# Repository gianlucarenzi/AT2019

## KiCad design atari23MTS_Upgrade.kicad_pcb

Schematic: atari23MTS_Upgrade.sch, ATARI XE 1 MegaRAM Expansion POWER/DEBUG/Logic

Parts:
C1: 10u; c_elec_5x5.3
C2: 22u; c_elec_5x5.3
C3: 47u; c_elec_5x5.3
CART1: ATARI-CARTRIDGE; ATARI-LEFT-CARTRIDGE
D1: LRED; LED_1206
D2: LYELLOW; LED_1206
DISABLE.MODE.1, DISABLE.MODE.2: CONN_01X02; Pin_Header_Straight_1x02
ECI1: ECIBUS; ATARI-XE-ECI-SLOT
EXTPWR1: CONN_01X04; Pin_Header_Angled_1x04
FT232RPi.1: CONN_01X03; Pin_Header_Straight_1x03
JP1, JP2: CONN_01X03; Pin_Header_Straight_1x03
L1, L2: INDUCTOR_SMALL; Choke_SMD_1206_Handsoldering
P1: CONN_01X01; Pin_Header_Straight_1x01
P2, P3, P4, P5: CONN_01X01; MountingHole
P6: CONN_01X01; Measurement_Point_Round-SMD-Pad_Small
R1: 330; R_1206_HandSoldering
R2, R4: 10K; R_1206_HandSoldering
R3: 220; R_1206_HandSoldering
STLinkV2.1, STLinkV2.2: CONN_01X04; Pin_Header_Angled_1x04
SW1, SW2: SW_Push; SW_SPST_FSMSM_3D
U1: NCP1117ST33T3G; SOT-223

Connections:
+5VDC: CART1.13 (VCC), ECI1.7 (VCC), EXTPWR1.1, L1.2, R1.1; also elsewhere on the board
A0: CART1.5 (A0); also elsewhere on the board
A1: CART1.4 (A1); also elsewhere on the board
A2: CART1.3 (A2); also elsewhere on the board
A3: CART1.2 (A3); also elsewhere on the board
A4: CART1.C (A4); also elsewhere on the board
A5: CART1.D (A5); also elsewhere on the board
A6: CART1.E (A6); also elsewhere on the board
A7: CART1.F (A7); also elsewhere on the board
A8: CART1.H (A8); also elsewhere on the board
A9: CART1.J (A9); also elsewhere on the board
A10: CART1.P (A10); also elsewhere on the board
A11: CART1.N (A11); also elsewhere on the board
A12: CART1.K (A12); also elsewhere on the board
A13: ECI1.D (A13); also elsewhere on the board
A14: ECI1.E (A14); also elsewhere on the board
A15: ECI1.F (A15); also elsewhere on the board
AUDIO: ECI1.5 (AUDIO); also elsewhere on the board
B02/PHI2: CART1.S (PHI2); also elsewhere on the board
BOOT0_CART: JP1.2; also elsewhere on the board
BOOT0_MEM: JP2.2; also elsewhere on the board
D0: CART1.10 (D0); also elsewhere on the board
D1: CART1.9 (D1); also elsewhere on the board
D2: CART1.8 (D2); also elsewhere on the board
D3: CART1.L (D3); also elsewhere on the board
D4: CART1.6 (D4); also elsewhere on the board
D5: CART1.7 (D5); also elsewhere on the board
D6: CART1.11 (D6); also elsewhere on the board
D7: CART1.M (D7); also elsewhere on the board
GND: C1.2, C2.2, C3.2, CART1.B (GND), D1.1 (K), D2.1 (K), DISABLE.MODE.1.2, DISABLE.MODE.2.2, ECI1.H (GND), EXTPWR1.2, EXTPWR1.3, FT232RPi.1.1, JP1.3, JP2.3, P1.1, STLinkV2.1.1, STLinkV2.2.1, SW1.1, SW2.1, U1.1 (GND); also elsewhere on the board
unnamed: C2.1, C3.1, L2.2, R3.1, U1.2 (VO)
unnamed: D1.2 (A), R1.2
unnamed: D2.2 (A), R3.2
R/~W: CART1.R (R/~W); also elsewhere on the board
RD4: CART1.A (RD4); also elsewhere on the board
RD5: CART1.14 (RD5); also elsewhere on the board
RSRVD: ECI1.A (RSRVD); also elsewhere on the board
SWDCLK_CART: STLinkV2.1.3; also elsewhere on the board
SWDCLK_MEM: STLinkV2.2.3; also elsewhere on the board
SWDIO_CART: STLinkV2.1.2; also elsewhere on the board
SWDIO_MEM: STLinkV2.2.2; also elsewhere on the board
TP1: P6.1; also elsewhere on the board
UART_RX: FT232RPi.1.2; also elsewhere on the board
UART_TX: FT232RPi.1.3; also elsewhere on the board
VCC3V3: JP1.1, JP2.1, L2.1, R2.2, R4.2, STLinkV2.1.4, STLinkV2.2.4; also elsewhere on the board
VCC5V: C1.1, L1.1, U1.3 (VI); also elsewhere on the board
nRESET_CART: DISABLE.MODE.1.1, R2.1, SW1.2; also elsewhere on the board
nRESET_MEM: DISABLE.MODE.2.1, R4.1, SW2.2; also elsewhere on the board
~CCTL: CART1.15 (~CCTL); also elsewhere on the board
~D1XX: ECI1.3 (~D1XX); also elsewhere on the board
~EXSEL: ECI1.1 (~EXSEL); also elsewhere on the board
~HALT: ECI1.C (~HALT); also elsewhere on the board
~IRQ: ECI1.B (~IRQ); also elsewhere on the board
~MPD: ECI1.4 (~MPD); also elsewhere on the board
~REF: ECI1.6 (~REF); also elsewhere on the board
~RST: ECI1.2 (~RST); also elsewhere on the board
~S4: CART1.1 (~S4); also elsewhere on the board
~S5: CART1.12 (~S5); also elsewhere on the board

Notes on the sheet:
POWER SECTION
DEBUG/PROGRAMMING SECTION MEMORY
ATARI CONNECTIONS
MOUNTING HOLES
BOOTSEL CART
RESET BUTTON CART
RESET BUTTON MEM
DEBUG/PROGRAMMING SECTION CART
BOOTSEL MEM

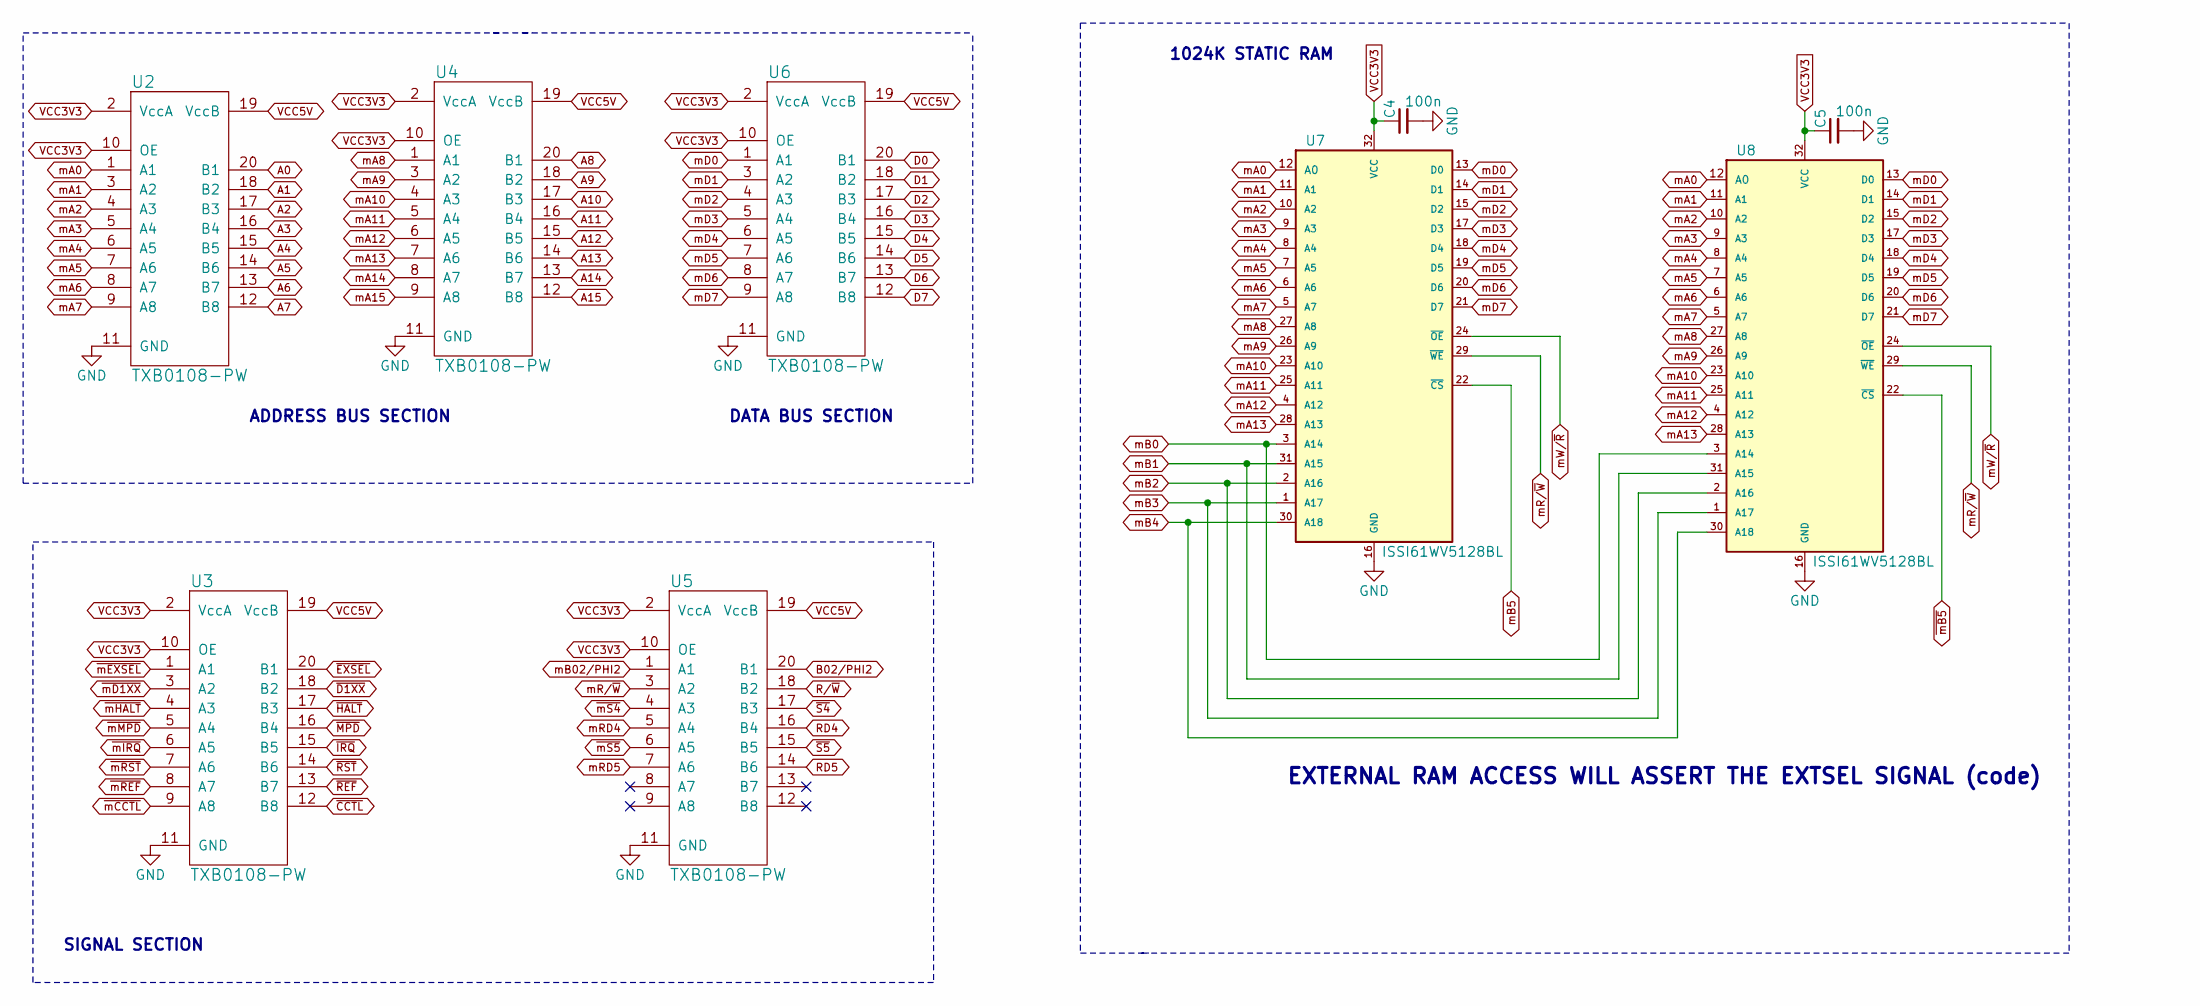
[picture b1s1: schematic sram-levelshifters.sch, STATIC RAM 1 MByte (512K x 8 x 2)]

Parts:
C4, C5: 100n; C_1206_HandSoldering
U2, U3, U4, U5, U6: TXB0108-PW; SSOP-20_4.4x6.5mm_Pitch0.65mm
U7, U8: ISSI61WV5128BL; SOP-32L-20.5x11.30-1.27mm

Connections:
A0: U2.20 (B1); also elsewhere on the board
A1: U2.18 (B2); also elsewhere on the board
A2: U2.17 (B3); also elsewhere on the board
A3: U2.16 (B4); also elsewhere on the board
A4: U2.15 (B5); also elsewhere on the board
A5: U2.14 (B6); also elsewhere on the board
A6: U2.13 (B7); also elsewhere on the board
A7: U2.12 (B8); also elsewhere on the board
A8: U4.20 (B1); also elsewhere on the board
A9: U4.18 (B2); also elsewhere on the board
A10: U4.17 (B3); also elsewhere on the board
A11: U4.16 (B4); also elsewhere on the board
A12: U4.15 (B5); also elsewhere on the board
A13: U4.14 (B6); also elsewhere on the board
A14: U4.13 (B7); also elsewhere on the board
A15: U4.12 (B8); also elsewhere on the board
B02/PHI2: U5.20 (B1); also elsewhere on the board
D0: U6.20 (B1); also elsewhere on the board
D1: U6.18 (B2); also elsewhere on the board
D2: U6.17 (B3); also elsewhere on the board
D3: U6.16 (B4); also elsewhere on the board
D4: U6.15 (B5); also elsewhere on the board
D5: U6.14 (B6); also elsewhere on the board
D6: U6.13 (B7); also elsewhere on the board
D7: U6.12 (B8); also elsewhere on the board
GND: C4.2, C5.2, U2.11 (GND), U3.11 (GND), U4.11 (GND), U5.11 (GND), U6.11 (GND), U7.16 (GND), U8.16 (GND); also elsewhere on the board
R/~W: U5.18 (B2); also elsewhere on the board
RD4: U5.16 (B4); also elsewhere on the board
RD5: U5.14 (B6); also elsewhere on the board
VCC3V3: C4.1, C5.1, U2.2 (VccA), U2.10 (OE), U3.2 (VccA), U3.10 (OE), U4.2 (VccA), U4.10 (OE), U5.2 (VccA), U5.10 (OE), U6.2 (VccA), U6.10 (OE), U7.32 (VCC), U8.32 (VCC); also elsewhere on the board
VCC5V: U2.19 (VccB), U3.19 (VccB), U4.19 (VccB), U5.19 (VccB), U6.19 (VccB); also elsewhere on the board
mA0: U2.1 (A1), U7.12 (A0), U8.12 (A0); also elsewhere on the board
mA1: U2.3 (A2), U7.11 (A1), U8.11 (A1); also elsewhere on the board
mA2: U2.4 (A3), U7.10 (A2), U8.10 (A2); also elsewhere on the board
mA3: U2.5 (A4), U7.9 (A3), U8.9 (A3); also elsewhere on the board
mA4: U2.6 (A5), U7.8 (A4), U8.8 (A4); also elsewhere on the board
mA5: U2.7 (A6), U7.7 (A5), U8.7 (A5); also elsewhere on the board
mA6: U2.8 (A7), U7.6 (A6), U8.6 (A6); also elsewhere on the board
mA7: U2.9 (A8), U7.5 (A7), U8.5 (A7); also elsewhere on the board
mA8: U4.1 (A1), U7.27 (A8), U8.27 (A8); also elsewhere on the board
mA9: U4.3 (A2), U7.26 (A9), U8.26 (A9); also elsewhere on the board
mA10: U4.4 (A3), U7.23 (A10), U8.23 (A10); also elsewhere on the board
mA11: U4.5 (A4), U7.25 (A11), U8.25 (A11); also elsewhere on the board
mA12: U4.6 (A5), U7.4 (A12), U8.4 (A12); also elsewhere on the board
mA13: U4.7 (A6), U7.28 (A13), U8.28 (A13); also elsewhere on the board
mA14: U4.8 (A7); also elsewhere on the board
mA15: U4.9 (A8); also elsewhere on the board
mB0: U7.3 (A14), U8.3 (A14); also elsewhere on the board
mB1: U7.31 (A15), U8.31 (A15); also elsewhere on the board
mB2: U7.2 (A16), U8.2 (A16); also elsewhere on the board
mB02/PHI2: U5.1 (A1); also elsewhere on the board
mB3: U7.1 (A17), U8.1 (A17); also elsewhere on the board
mB4: U7.30 (A18), U8.30 (A18); also elsewhere on the board
mB5: U7.22 (~CS); also elsewhere on the board
mD0: U6.1 (A1), U7.13 (D0), U8.13 (D0); also elsewhere on the board
mD1: U6.3 (A2), U7.14 (D1), U8.14 (D1); also elsewhere on the board
mD2: U6.4 (A3), U7.15 (D2), U8.15 (D2); also elsewhere on the board
mD3: U6.5 (A4), U7.17 (D3), U8.17 (D3); also elsewhere on the board
mD4: U6.6 (A5), U7.18 (D4), U8.18 (D4); also elsewhere on the board
mD5: U6.7 (A6), U7.19 (D5), U8.19 (D5); also elsewhere on the board
mD6: U6.8 (A7), U7.20 (D6), U8.20 (D6); also elsewhere on the board
mD7: U6.9 (A8), U7.21 (D7), U8.21 (D7); also elsewhere on the board
mR/~W: U5.3 (A2), U7.29 (~WE), U8.29 (~WE); also elsewhere on the board
mRD4: U5.5 (A4); also elsewhere on the board
mRD5: U5.7 (A6); also elsewhere on the board
mW/~R: U7.24 (~OE), U8.24 (~OE); also elsewhere on the board
~CCTL: U3.12 (B8); also elsewhere on the board
~D1XX: U3.18 (B2); also elsewhere on the board
~EXSEL: U3.20 (B1); also elsewhere on the board
~HALT: U3.17 (B3); also elsewhere on the board
~IRQ: U3.15 (B5); also elsewhere on the board
~MPD: U3.16 (B4); also elsewhere on the board
~REF: U3.13 (B7); also elsewhere on the board
~RST: U3.14 (B6); also elsewhere on the board
~S4: U5.17 (B3); also elsewhere on the board
~S5: U5.15 (B5); also elsewhere on the board
~mB5: U8.22 (~CS); also elsewhere on the board
~mCCTL: U3.9 (A8); also elsewhere on the board
~mD1XX: U3.3 (A2); also elsewhere on the board
~mEXSEL: U3.1 (A1); also elsewhere on the board
~mHALT: U3.4 (A3); also elsewhere on the board
~mIRQ: U3.6 (A5); also elsewhere on the board
~mMPD: U3.5 (A4); also elsewhere on the board
~mREF: U3.8 (A7); also elsewhere on the board
~mRST: U3.7 (A6); also elsewhere on the board
~mS4: U5.4 (A3); also elsewhere on the board
~mS5: U5.6 (A5); also elsewhere on the board

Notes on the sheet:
ADDRESS BUS SECTION
DATA BUS SECTION
SIGNAL SECTION
1024K STATIC RAM
EXTERNAL RAM ACCESS WILL ASSERT THE EXTSEL SIGNAL (code)

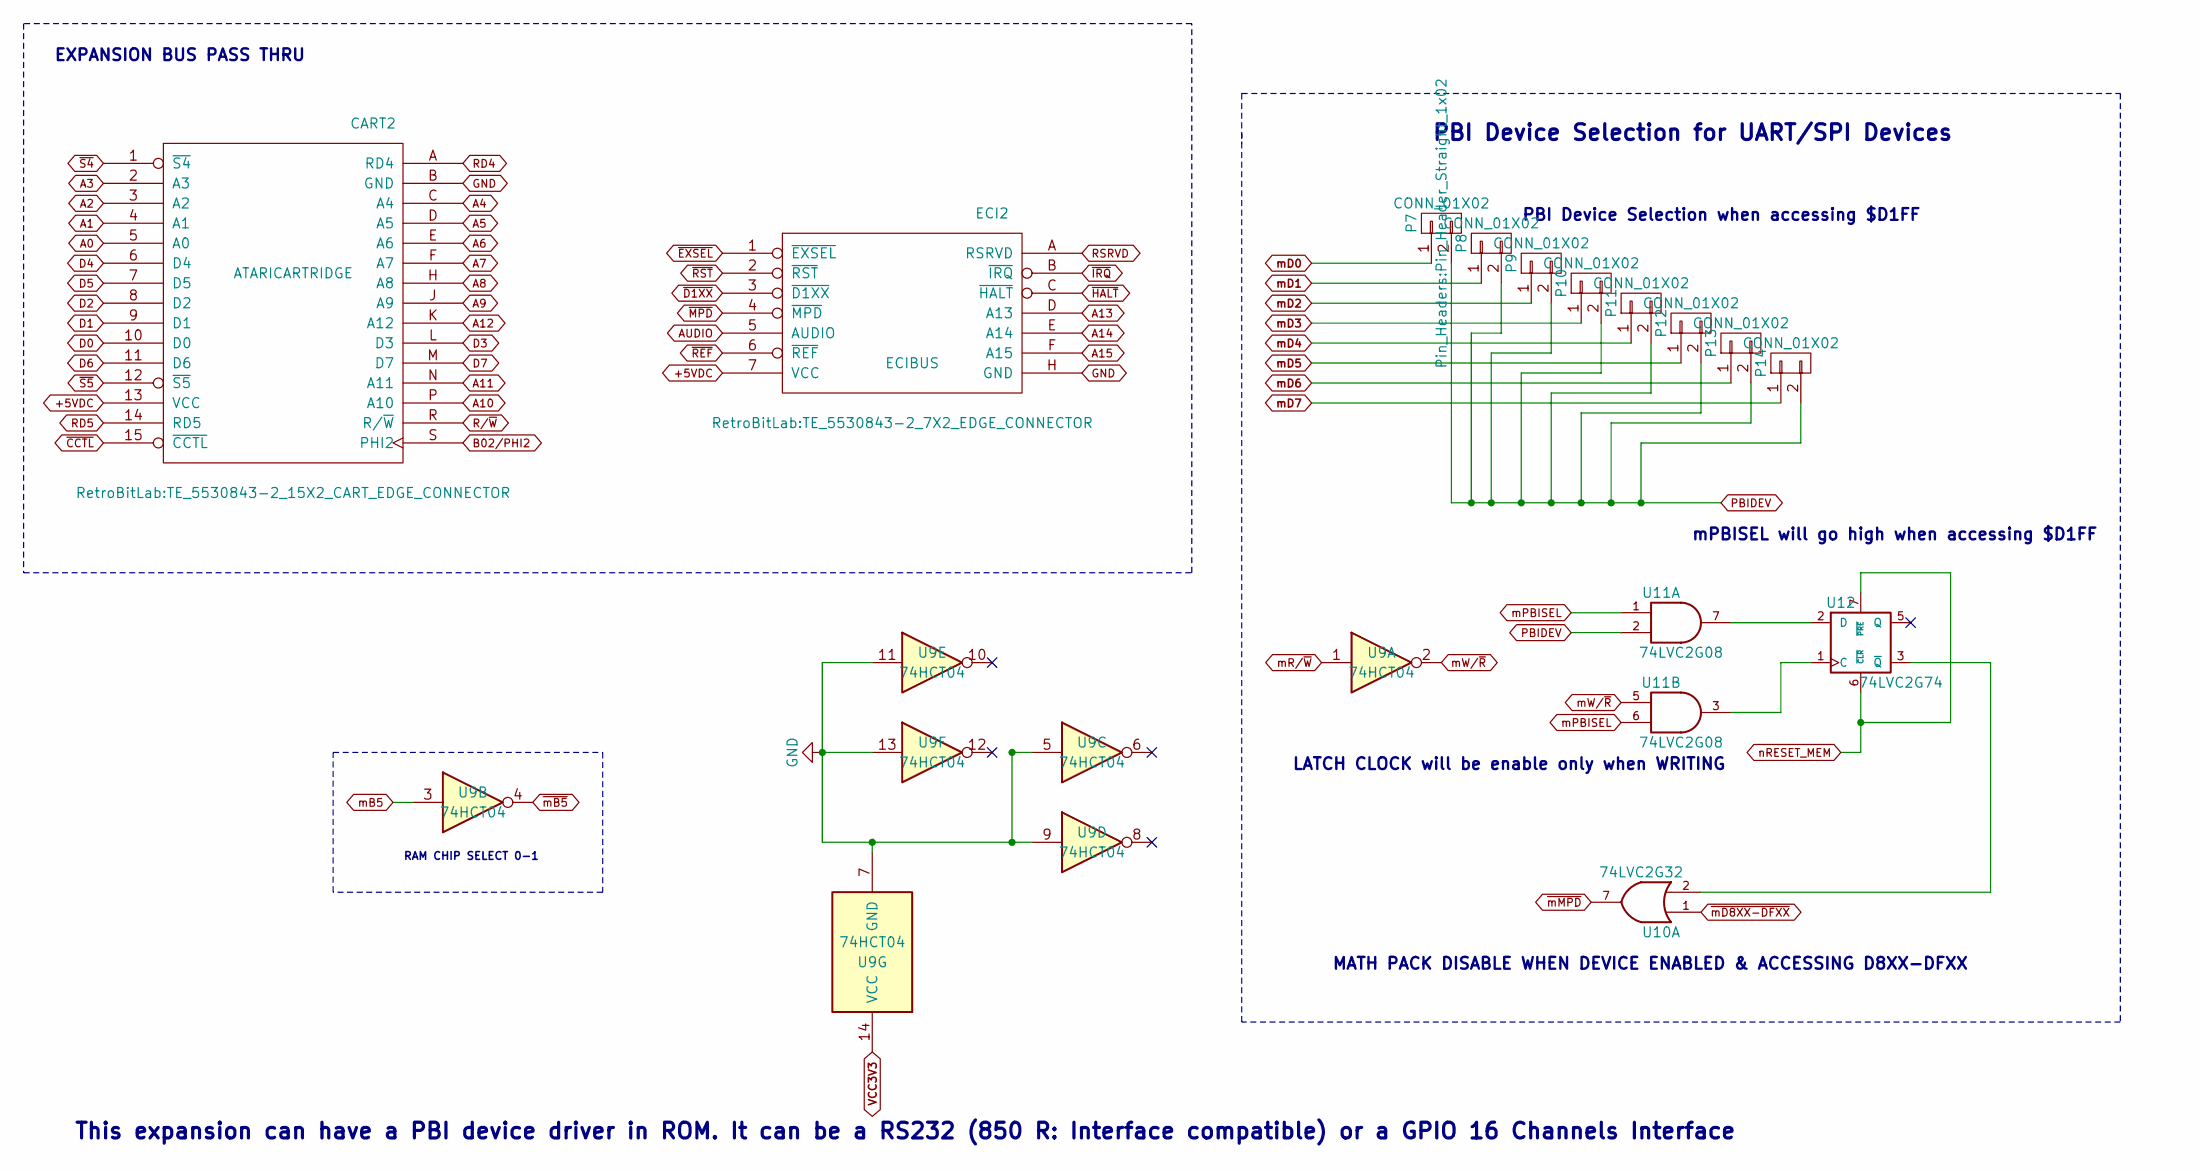
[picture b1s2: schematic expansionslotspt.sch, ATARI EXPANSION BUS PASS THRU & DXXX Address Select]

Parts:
CART2: ATARICARTRIDGE; TE_5530843-2_15X2_CART_EDGE_CONNECTOR
ECI2: ECIBUS; TE_5530843-2_7X2_EDGE_CONNECTOR
P7, P8, P9, P10, P11, P12, P13, P14: CONN_01X02; Pin_Header_Straight_1x02
U9: 74HCT04; SSOP-14_5.3x6.2mm_Pitch0.65mm
U10: 74LVC2G32; TSSOP-8_3x3mm_Pitch0.65mm
U11: 74LVC2G08; TSSOP-8_3x3mm_Pitch0.65mm
U12: 74LVC2G74; TSSOP-8_3x3mm_Pitch0.65mm

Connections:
+5VDC: CART2.13 (VCC), ECI2.7 (VCC), U10.8 (VCC), U11.8 (VCC), U12.8 (VCC); also elsewhere on the board
A0: CART2.5 (A0); also elsewhere on the board
A1: CART2.4 (A1); also elsewhere on the board
A2: CART2.3 (A2); also elsewhere on the board
A3: CART2.2 (A3); also elsewhere on the board
A4: CART2.C (A4); also elsewhere on the board
A5: CART2.D (A5); also elsewhere on the board
A6: CART2.E (A6); also elsewhere on the board
A7: CART2.F (A7); also elsewhere on the board
A8: CART2.H (A8); also elsewhere on the board
A9: CART2.J (A9); also elsewhere on the board
A10: CART2.P (A10); also elsewhere on the board
A11: CART2.N (A11); also elsewhere on the board
A12: CART2.K (A12); also elsewhere on the board
A13: ECI2.D (A13); also elsewhere on the board
A14: ECI2.E (A14); also elsewhere on the board
A15: ECI2.F (A15); also elsewhere on the board
AUDIO: ECI2.5 (AUDIO); also elsewhere on the board
B02/PHI2: CART2.S (PHI2); also elsewhere on the board
D0: CART2.10 (D0); also elsewhere on the board
D1: CART2.9 (D1); also elsewhere on the board
D2: CART2.8 (D2); also elsewhere on the board
D3: CART2.L (D3); also elsewhere on the board
D4: CART2.6 (D4); also elsewhere on the board
D5: CART2.7 (D5); also elsewhere on the board
D6: CART2.11 (D6); also elsewhere on the board
D7: CART2.M (D7); also elsewhere on the board
GND: CART2.B (GND), ECI2.H (GND), U9.5, U9.7 (GND), U9.9, U9.11, U9.13, U10.4 (GND), U11.4 (GND), U12.4 (GND); also elsewhere on the board
unnamed: U10.2, U12.3 (~Q)
unnamed: U11.3, U12.1 (C)
unnamed: U11.7, U12.2 (D)
PBIDEV: P7.2, P8.2, P9.2, P10.2, P11.2, P12.2, P13.2, P14.2, U11.2
R/~W: CART2.R (R/~W); also elsewhere on the board
RD4: CART2.A (RD4); also elsewhere on the board
RD5: CART2.14 (RD5); also elsewhere on the board
RSRVD: ECI2.A (RSRVD); also elsewhere on the board
VCC3V3: U9.14 (VCC); also elsewhere on the board
mB5: U9.3; also elsewhere on the board
mD0: P7.1; also elsewhere on the board
mD1: P8.1; also elsewhere on the board
mD2: P9.1; also elsewhere on the board
mD3: P10.1; also elsewhere on the board
mD4: P11.1; also elsewhere on the board
mD5: P12.1; also elsewhere on the board
mD6: P13.1; also elsewhere on the board
mD7: P14.1; also elsewhere on the board
mPBISEL: U11.1, U11.6; also elsewhere on the board
mR/~W: U9.1; also elsewhere on the board
mW/~R: U9.2, U11.5; also elsewhere on the board
nRESET_MEM: U12.6 (~CLR), U12.7 (~PRE); also elsewhere on the board
~CCTL: CART2.15 (~CCTL); also elsewhere on the board
~D1XX: ECI2.3 (~D1XX); also elsewhere on the board
~EXSEL: ECI2.1 (~EXSEL); also elsewhere on the board
~HALT: ECI2.C (~HALT); also elsewhere on the board
~IRQ: ECI2.B (~IRQ); also elsewhere on the board
~MPD: ECI2.4 (~MPD); also elsewhere on the board
~REF: ECI2.6 (~REF); also elsewhere on the board
~RST: ECI2.2 (~RST); also elsewhere on the board
~S4: CART2.1 (~S4); also elsewhere on the board
~S5: CART2.12 (~S5); also elsewhere on the board
~mB5: U9.4; also elsewhere on the board
~mD8XX-DFXX: U10.1; also elsewhere on the board
~mMPD: U10.7; also elsewhere on the board

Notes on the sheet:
EXPANSION BUS PASS THRU
PBI Device Selection when accessing $D1FF
MATH PACK DISABLE WHEN DEVICE ENABLED & ACCESSING D8XX-DFXX
mPBISEL will go high when accessing $D1FF
LATCH CLOCK will be enable only when WRITING
PBI Device Selection for UART/SPI Devices
This expansion can have a PBI device driver in ROM. It can be a RS232 (850 R: Interface compatible) or a GPIO 16 Channels Interface
RAM CHIP SELECT 0-1

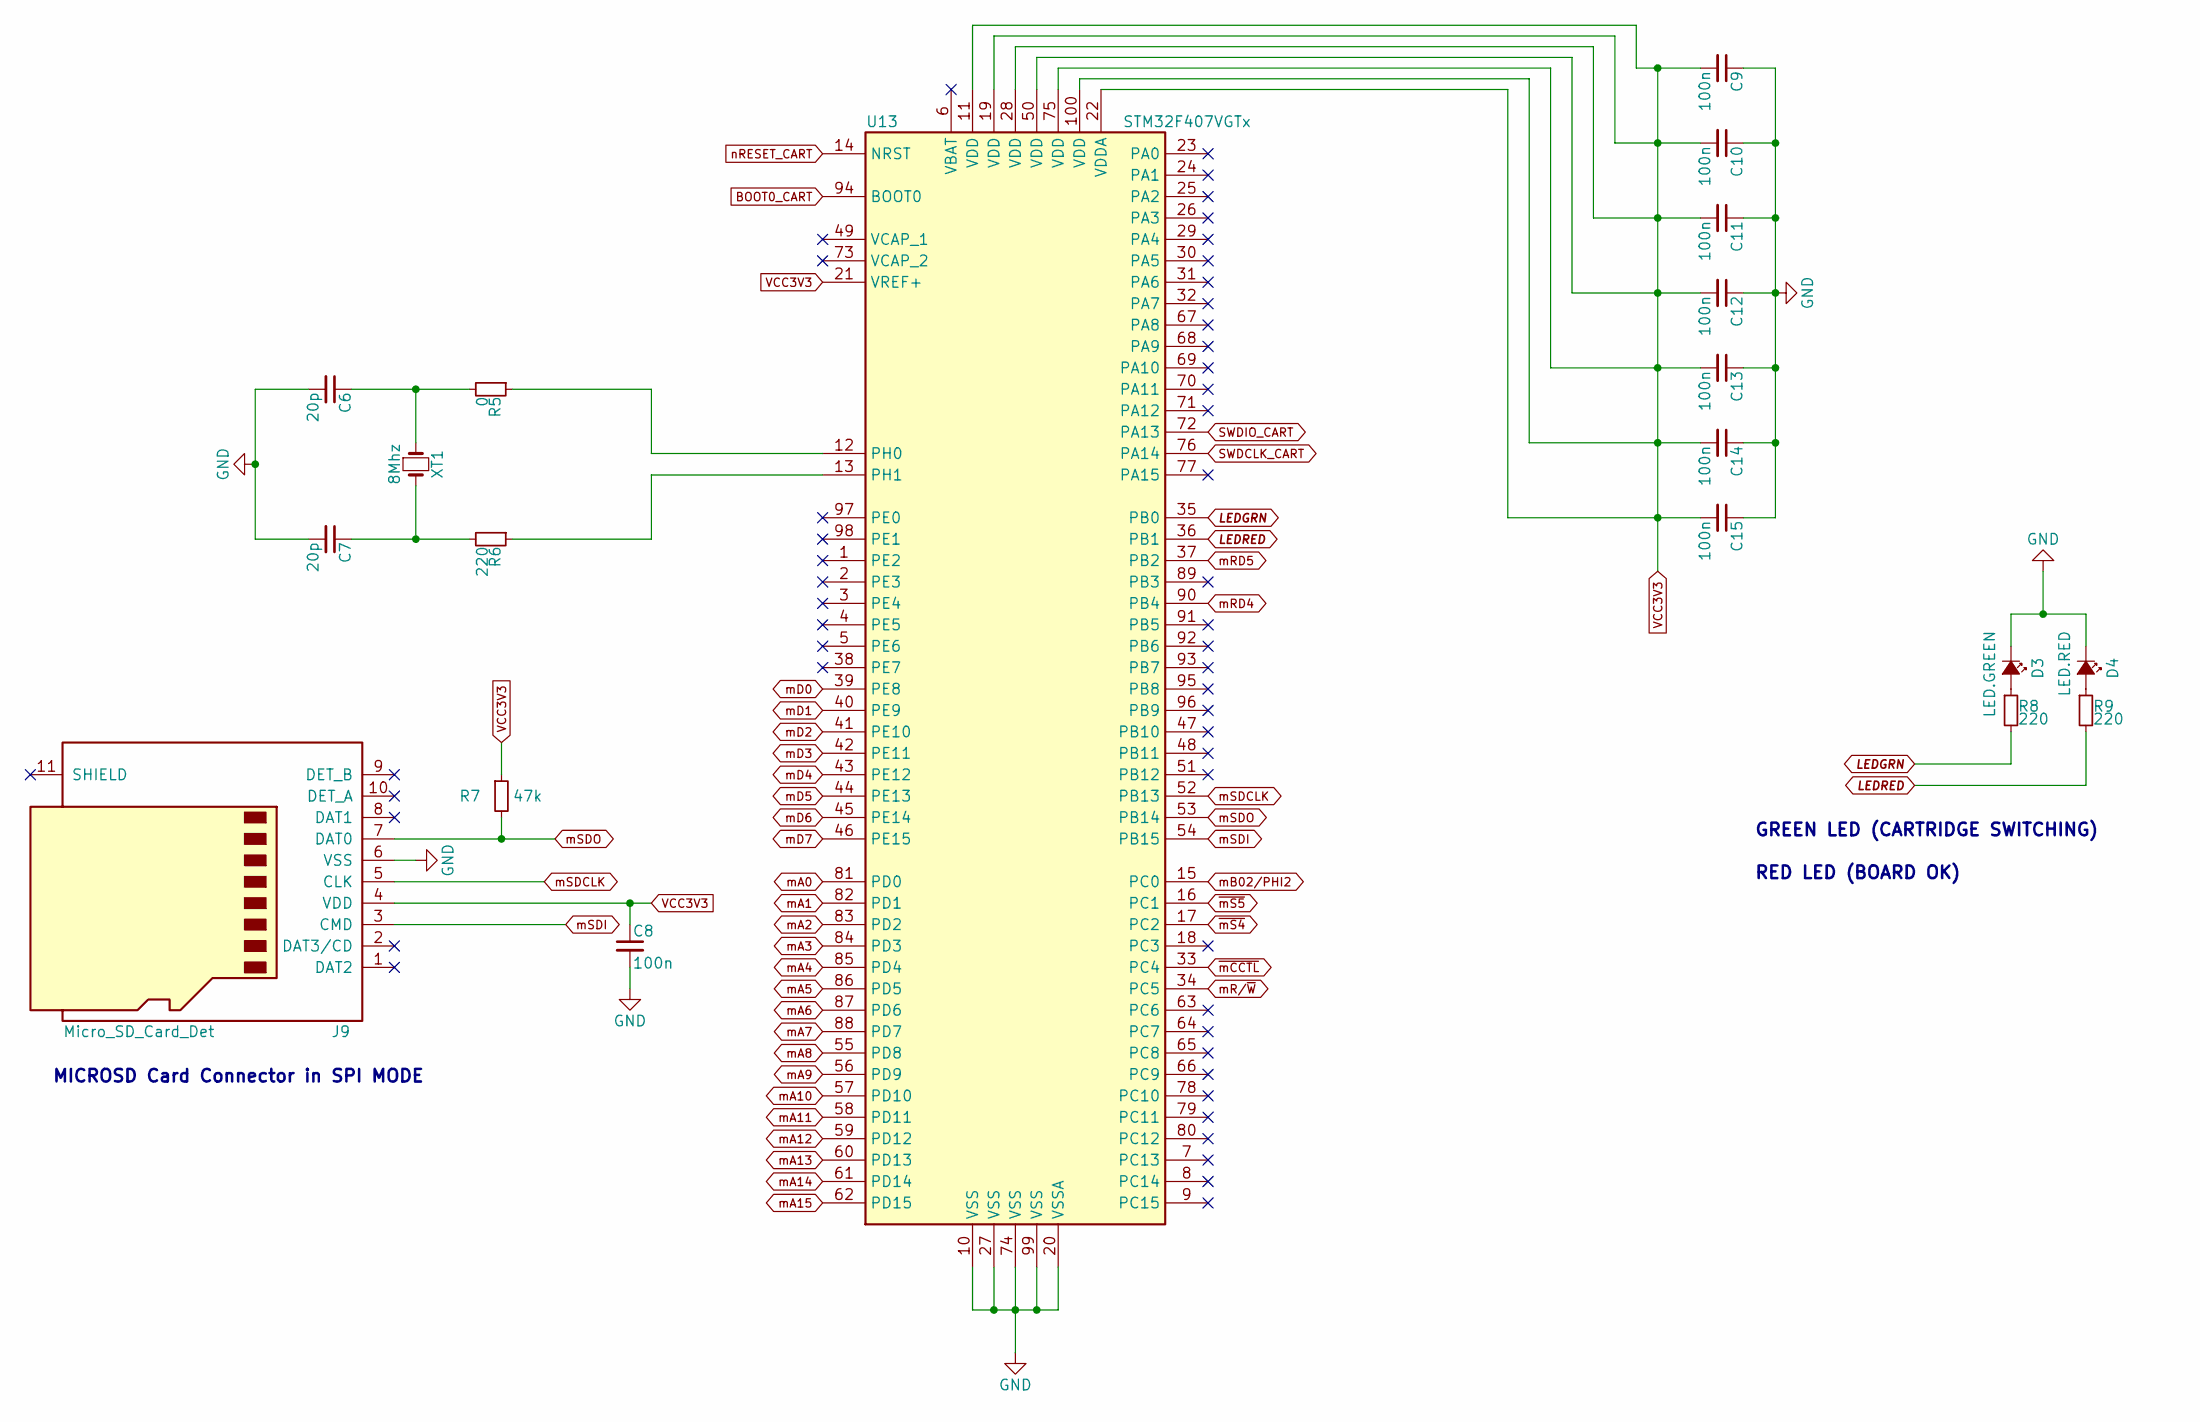
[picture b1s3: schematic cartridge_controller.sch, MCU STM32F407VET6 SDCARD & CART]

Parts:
C6, C7: 20p; C_1206_HandSoldering
C8, C9, C10, C11, C12, C13, C14, C15: 100n; C_1206_HandSoldering
D3: LED.GREEN; LED_1206
D4: LED.RED; LED_1206
J9: Micro_SD_Card_Det; microSD_HC_Hirose_DM3D-SF
R5: 0; R_1206_HandSoldering
R6, R8, R9: 220; R_1206_HandSoldering
R7: 47k; R_1206_HandSoldering
U13: STM32F407VGTx; TQFP-100_14x14mm_Pitch0.5mm
XT1: 8Mhz; Crystal_HC49-4H_Vertical_3D

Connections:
BOOT0_CART: U13.94 (BOOT0); also elsewhere on the board
GND: C6.2, C7.2, C8.2, C9.1, C10.1, C11.1, C12.1, C13.1, C14.1, C15.1, D3.1 (K), D4.1 (K), J9.6 (VSS), U13.10 (VSS), U13.20 (VSSA), U13.27 (VSS), U13.74 (VSS), U13.99 (VSS); also elsewhere on the board
LEDGRN: R8.2, U13.35 (PB0)
LEDRED: R9.2, U13.36 (PB1)
unnamed: C6.1, R5.2, XT1.1
unnamed: C7.1, R6.2, XT1.2
unnamed: D3.2 (A), R8.1
unnamed: D4.2 (A), R9.1
unnamed: R5.1, U13.12 (PH0)
unnamed: R6.1, U13.13 (PH1)
SWDCLK_CART: U13.76 (PA14); also elsewhere on the board
SWDIO_CART: U13.72 (PA13); also elsewhere on the board
VCC3V3: C8.1, C9.2, C10.2, C11.2, C12.2, C13.2, C14.2, C15.2, J9.4 (VDD), R7.1, U13.11 (VDD), U13.19 (VDD), U13.21 (VREF+), U13.22 (VDDA), U13.28 (VDD), U13.50 (VDD), U13.75 (VDD), U13.100 (VDD); also elsewhere on the board
mA0: U13.81 (PD0); also elsewhere on the board
mA1: U13.82 (PD1); also elsewhere on the board
mA2: U13.83 (PD2); also elsewhere on the board
mA3: U13.84 (PD3); also elsewhere on the board
mA4: U13.85 (PD4); also elsewhere on the board
mA5: U13.86 (PD5); also elsewhere on the board
mA6: U13.87 (PD6); also elsewhere on the board
mA7: U13.88 (PD7); also elsewhere on the board
mA8: U13.55 (PD8); also elsewhere on the board
mA9: U13.56 (PD9); also elsewhere on the board
mA10: U13.57 (PD10); also elsewhere on the board
mA11: U13.58 (PD11); also elsewhere on the board
mA12: U13.59 (PD12); also elsewhere on the board
mA13: U13.60 (PD13); also elsewhere on the board
mA14: U13.61 (PD14); also elsewhere on the board
mA15: U13.62 (PD15); also elsewhere on the board
mB02/PHI2: U13.15 (PC0); also elsewhere on the board
mD0: U13.39 (PE8); also elsewhere on the board
mD1: U13.40 (PE9); also elsewhere on the board
mD2: U13.41 (PE10); also elsewhere on the board
mD3: U13.42 (PE11); also elsewhere on the board
mD4: U13.43 (PE12); also elsewhere on the board
mD5: U13.44 (PE13); also elsewhere on the board
mD6: U13.45 (PE14); also elsewhere on the board
mD7: U13.46 (PE15); also elsewhere on the board
mR/~W: U13.34 (PC5); also elsewhere on the board
mRD4: U13.90 (PB4); also elsewhere on the board
mRD5: U13.37 (PB2); also elsewhere on the board
mSDCLK: J9.5 (CLK), U13.52 (PB13)
mSDI: J9.3 (CMD), U13.54 (PB15)
mSDO: J9.7 (DAT0), R7.2, U13.53 (PB14)
nRESET_CART: U13.14 (NRST); also elsewhere on the board
~mCCTL: U13.33 (PC4); also elsewhere on the board
~mS4: U13.17 (PC2); also elsewhere on the board
~mS5: U13.16 (PC1); also elsewhere on the board

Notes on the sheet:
GREEN LED (CARTRIDGE SWITCHING)
RED LED (BOARD OK)
MICROSD Card Connector in SPI MODE

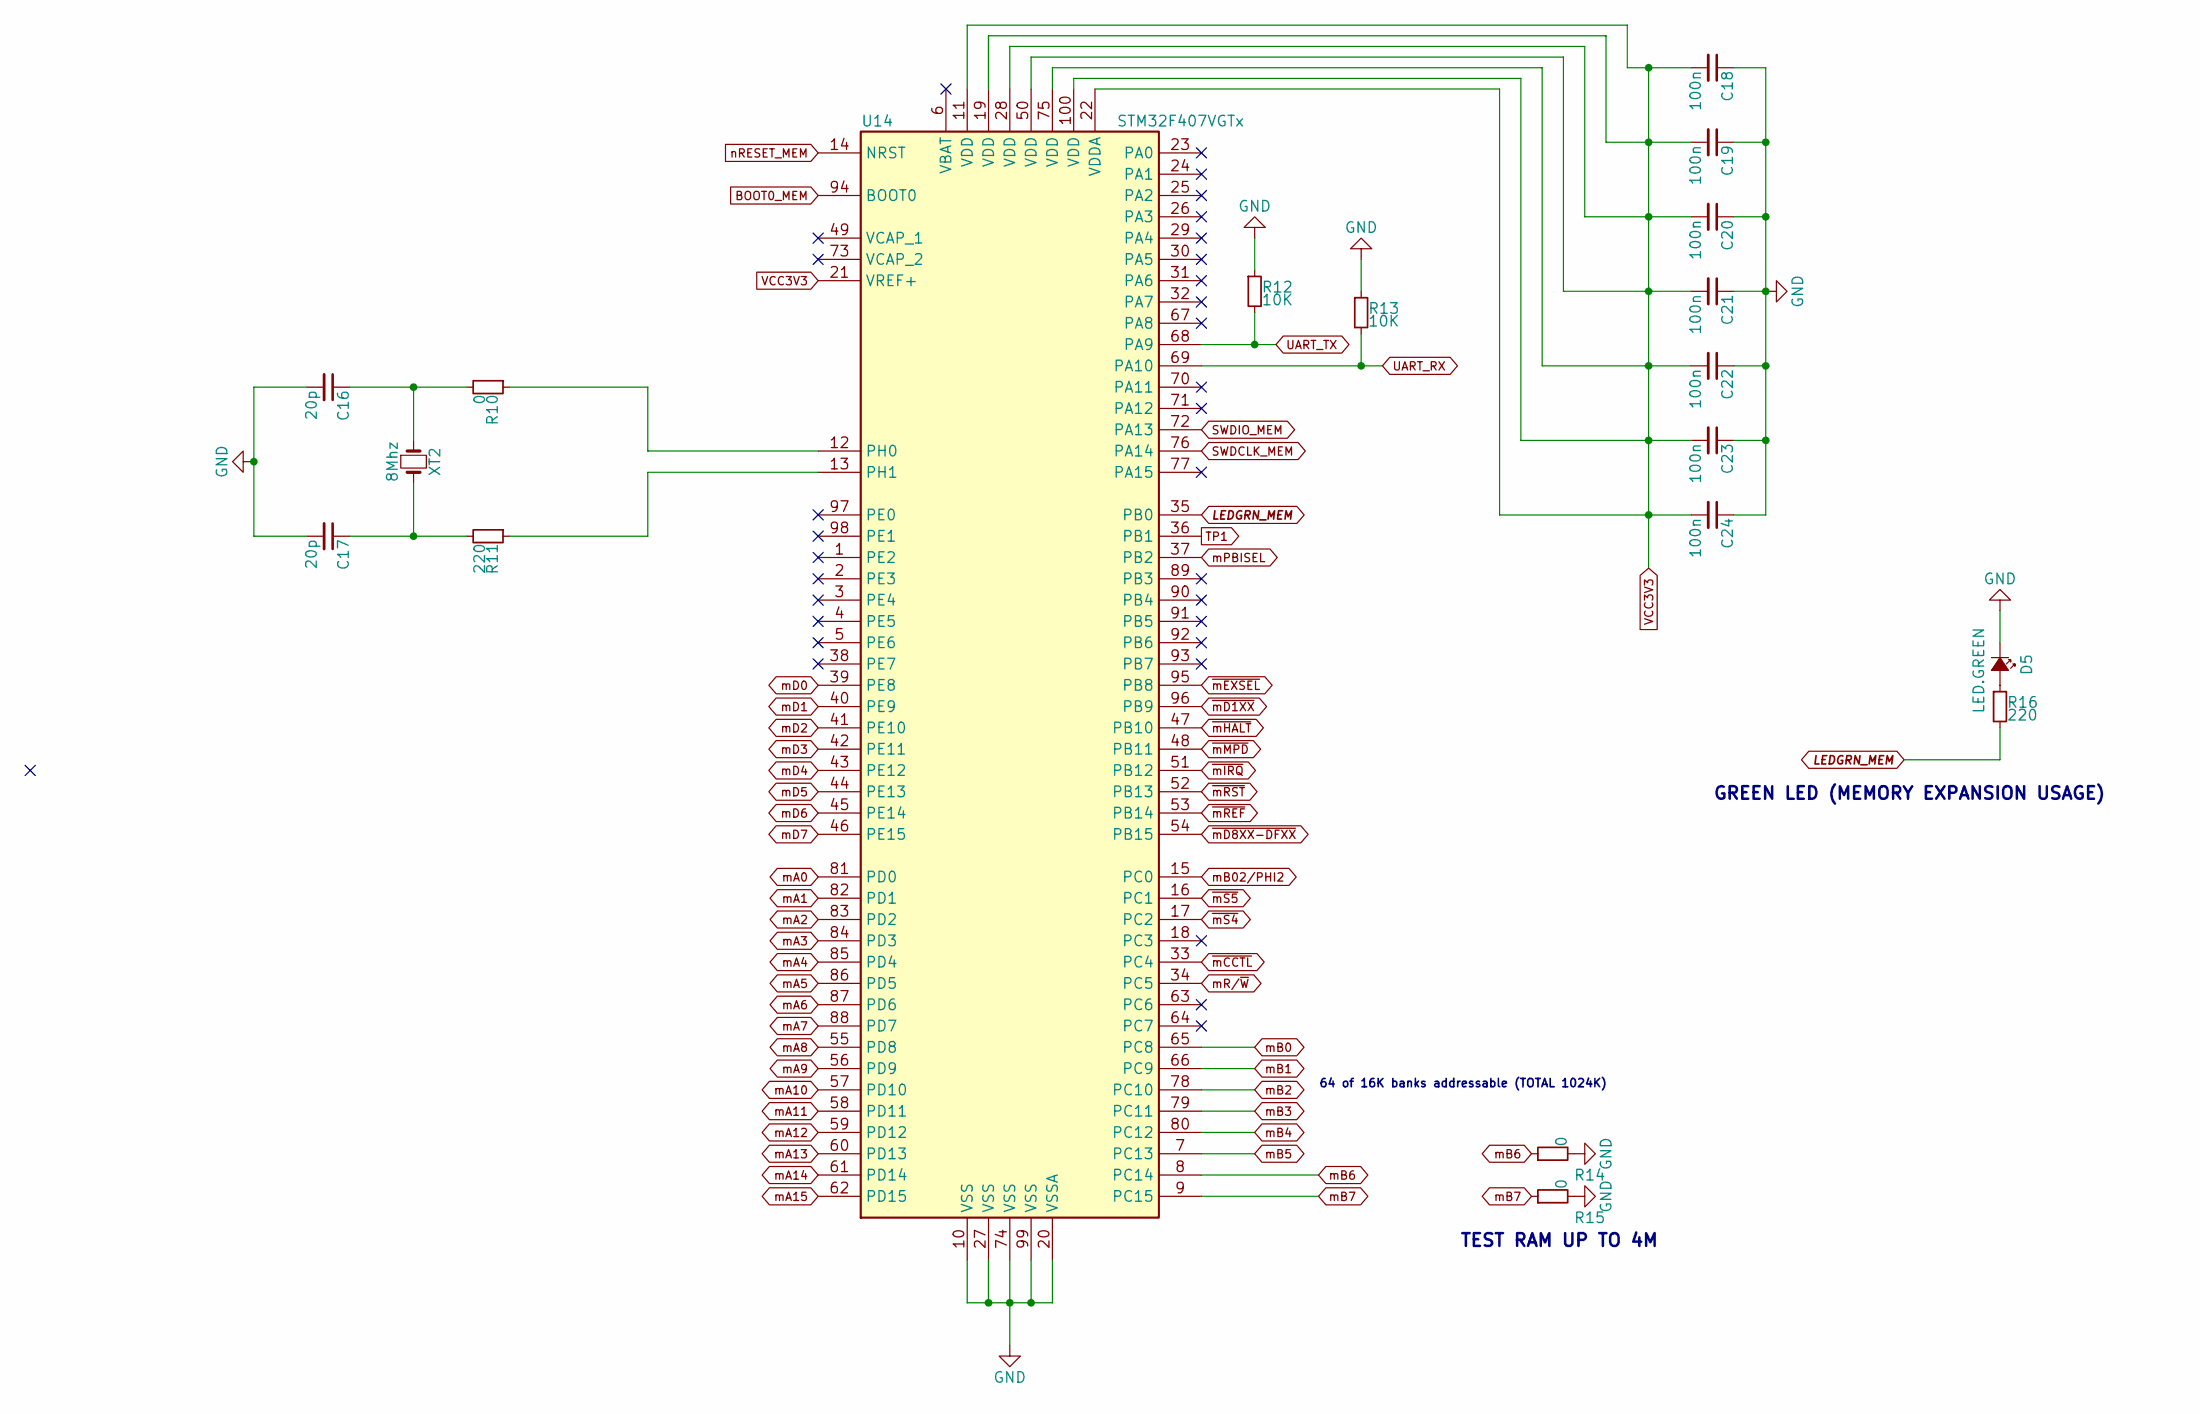
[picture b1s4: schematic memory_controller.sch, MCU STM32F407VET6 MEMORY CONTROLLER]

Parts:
C16, C17: 20p; C_1206_HandSoldering
C18, C19, C20, C21, C22, C23, C24: 100n; C_1206_HandSoldering
D5: LED.GREEN; LED_1206
R10, R14, R15: 0; R_1206_HandSoldering
R11, R16: 220; R_1206_HandSoldering
R12, R13: 10K; R_1206_HandSoldering
U14: STM32F407VGTx; TQFP-100_14x14mm_Pitch0.5mm
XT2: 8Mhz; Crystal_HC49-4H_Vertical_3D

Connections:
BOOT0_MEM: U14.94 (BOOT0); also elsewhere on the board
GND: C16.2, C17.2, C18.1, C19.1, C20.1, C21.1, C22.1, C23.1, C24.1, D5.1 (K), R12.1, R13.1, R14.2, R15.2, U14.10 (VSS), U14.20 (VSSA), U14.27 (VSS), U14.74 (VSS), U14.99 (VSS); also elsewhere on the board
LEDGRN_MEM: R16.2, U14.35 (PB0)
unnamed: C16.1, R10.2, XT2.1
unnamed: C17.1, R11.2, XT2.2
unnamed: D5.2 (A), R16.1
unnamed: R10.1, U14.12 (PH0)
unnamed: R11.1, U14.13 (PH1)
SWDCLK_MEM: U14.76 (PA14); also elsewhere on the board
SWDIO_MEM: U14.72 (PA13); also elsewhere on the board
TP1: U14.36 (PB1); also elsewhere on the board
UART_RX: R13.2, U14.69 (PA10); also elsewhere on the board
UART_TX: R12.2, U14.68 (PA9); also elsewhere on the board
VCC3V3: C18.2, C19.2, C20.2, C21.2, C22.2, C23.2, C24.2, U14.11 (VDD), U14.19 (VDD), U14.21 (VREF+), U14.22 (VDDA), U14.28 (VDD), U14.50 (VDD), U14.75 (VDD), U14.100 (VDD); also elsewhere on the board
mA0: U14.81 (PD0); also elsewhere on the board
mA1: U14.82 (PD1); also elsewhere on the board
mA2: U14.83 (PD2); also elsewhere on the board
mA3: U14.84 (PD3); also elsewhere on the board
mA4: U14.85 (PD4); also elsewhere on the board
mA5: U14.86 (PD5); also elsewhere on the board
mA6: U14.87 (PD6); also elsewhere on the board
mA7: U14.88 (PD7); also elsewhere on the board
mA8: U14.55 (PD8); also elsewhere on the board
mA9: U14.56 (PD9); also elsewhere on the board
mA10: U14.57 (PD10); also elsewhere on the board
mA11: U14.58 (PD11); also elsewhere on the board
mA12: U14.59 (PD12); also elsewhere on the board
mA13: U14.60 (PD13); also elsewhere on the board
mA14: U14.61 (PD14); also elsewhere on the board
mA15: U14.62 (PD15); also elsewhere on the board
mB0: U14.65 (PC8); also elsewhere on the board
mB1: U14.66 (PC9); also elsewhere on the board
mB2: U14.78 (PC10); also elsewhere on the board
mB02/PHI2: U14.15 (PC0); also elsewhere on the board
mB3: U14.79 (PC11); also elsewhere on the board
mB4: U14.80 (PC12); also elsewhere on the board
mB5: U14.7 (PC13); also elsewhere on the board
mB6: R14.1, U14.8 (PC14)
mB7: R15.1, U14.9 (PC15)
mD0: U14.39 (PE8); also elsewhere on the board
mD1: U14.40 (PE9); also elsewhere on the board
mD2: U14.41 (PE10); also elsewhere on the board
mD3: U14.42 (PE11); also elsewhere on the board
mD4: U14.43 (PE12); also elsewhere on the board
mD5: U14.44 (PE13); also elsewhere on the board
mD6: U14.45 (PE14); also elsewhere on the board
mD7: U14.46 (PE15); also elsewhere on the board
mPBISEL: U14.37 (PB2); also elsewhere on the board
mR/~W: U14.34 (PC5); also elsewhere on the board
nRESET_MEM: U14.14 (NRST); also elsewhere on the board
~mCCTL: U14.33 (PC4); also elsewhere on the board
~mD1XX: U14.96 (PB9); also elsewhere on the board
~mD8XX-DFXX: U14.54 (PB15); also elsewhere on the board
~mEXSEL: U14.95 (PB8); also elsewhere on the board
~mHALT: U14.47 (PB10); also elsewhere on the board
~mIRQ: U14.51 (PB12); also elsewhere on the board
~mMPD: U14.48 (PB11); also elsewhere on the board
~mREF: U14.53 (PB14); also elsewhere on the board
~mRST: U14.52 (PB13); also elsewhere on the board
~mS4: U14.17 (PC2); also elsewhere on the board
~mS5: U14.16 (PC1); also elsewhere on the board

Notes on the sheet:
GREEN LED (MEMORY EXPANSION USAGE)
64 of 16K banks addressable (TOTAL 1024K)
TEST RAM UP TO 4M

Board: 2 copper layers, 92 parts (0 on the bottom side), 129 nets, no tracks yet.
